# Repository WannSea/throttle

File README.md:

# WannSea Gashebel Firmware

Dieses Projekt nutzt das https://github.com/rp-rs/rp2040-project-template als Template.

## Installation

Rust über https://rustup.rs/ installieren und anschließend ausführen:

```sh
rustup target install thumbv6m-none-eabi
cargo install flip-link
cargo install --locked elf2uf2-rs
```

## Build

Es gibt zwei Möglichkeiten:

1. Den RP2040 mit gedrückter BOOTSEL-Taste per USB verbinden und die Firmware direkt bauen und flashen:

   ```sh
   cargo run
   ```

2. Eine UF2-Datei bauen, die später manuell auf das RP2040-USB-Laufwerk kopiert werden kann:

   ```sh
   cargo build --release
   elf2uf2-rs target/thumbv6m-none-eabi/release/rp2040-project-template throttle.uf2
   ```

## Info:

Green LED Blinking: Sending CAN throttle command
Red LED: Lever Locked

## Encoder / Hall

Der verwendete Encoder mit dem 5-poligen Stecker ist ein AS5600 und wird über I2C gelesen:

- Board-Stecker: `SDA`, `SCL`, `PWM/OUT`, `GND`, `3V3`
- Am AS5600: `VCC -> 3V3`, `GND -> GND`, `SDA -> SDA`, `SCL -> SCL`
- `DIR` habe ich fest mit `VCC` verbunden.
- `OUT/PWM` wird von der Firmware aktuell nicht benutzt.

## Veränderbare Parameter

Die wichtigsten Parameter stehen am Anfang von `src/main.rs`:

- `MAX_CURRENT_A`: maximal ausgegebener Strom bei vollständig ausgelenktem Gashebel, aktuell `500.0` A.
- `DELAY_MS`: Zeit zwischen zwei Ausgaben. `20` ms entsprechen 50 Hz.
- `ENCODER_ZERO_RAW`: Raw-Wert des Encoders in der neutralen Hebelposition.
- `ENCODER_FORWARD_MAX_RAW`: Raw-Wert bei vollständig nach vorne gedrücktem Gashebel.
- `ENCODER_REVERSE_MAX_RAW`: Raw-Wert bei vollständig nach hinten gedrücktem Gashebel.
- `ENCODER_DEADZONE_COUNTS`: Totzone von der Neutralstellung aus in jede Richtung. `50` bedeutet ungefähr 100 Counts Gesamttotzone.
- `PRETEND_HALL_PIN_ON`: Bei `true` wird der Hall-/Kill-Cord-Eingang für Tests als dauerhaft vorhanden behandelt.
- `ENABLE_USB_LOGGING`: Aktiviert bei `true` die Ausgabe der Encoderwerte über USB-Serial.

Die Encoder-Endwerte dürfen je nach Einbaurichtung des Sensors größer oder kleiner als `ENCODER_ZERO_RAW` sein. Entscheidend ist, dass die Werte an den tatsächlichen Endpositionen des Hebels eingetragen werden.

## USB-Debug-Ausgabe

Bei aktiviertem `ENABLE_USB_LOGGING` wird beispielsweise folgende Zeile ausgegeben:

```text
encoder raw: 2237, throttle_milli: 0, can: 00000116#00000000
```

Die drei Werte bedeuten:

- `encoder raw`: unverarbeiteter 12-Bit-Messwert des AS5600 von `0` bis `4095`.
- `throttle_milli`: aus Kalibrierung und Totzone berechnete Gasstellung. `-1000` entspricht dem einen Endanschlag, `0` der Neutralstellung und `+1000` dem anderen Endanschlag.
- `can`: Vorschau der tatsächlich gesendeten CAN-Nachricht im Format `CAN-ID#Payload`. `00000116` ist die `SetCurrent`-Nachricht für VESC-ID 22. Der achtstellige Payload enthält den vorzeichenbehafteten Stromwert als Ampere × 1.000. Im gesperrten Zustand ist dieser Payload immer `00000000`.

## SetDuty- und SetCurrent-Version

| SetDuty-Version | Aktuelle SetCurrent-Version |
|---|---|
| VESC `SetDuty`, CAN-ID `0x16` | VESC `SetCurrent`, CAN-ID `0x116` |
| Payload: vorzeichenbehafteter Duty-Wert von −100.000 bis +100.000 | Payload: vorzeichenbehafteter Stromwert von −500.000 bis +500.000 (Ampere × 1.000) |
| 50 Werte großes Glättungsfenster | Keine Glättung und keine Rampe |
| Vollständige Rampe dauert ca. 1 Sekunde | Ausgang folgt dem Gashebel unmittelbar |
| Ausgabe alle 20 ms / 50 Hz | Ausgabe alle 20 ms / 50 Hz |
| Null und der gesperrte Zustand werden explizit gesendet | Null und der gesperrte Zustand werden explizit gesendet |
| Encoder- und Hall-Auswertung wie in der aktuellen Version | Encoder- und Hall-Auswertung unverändert |

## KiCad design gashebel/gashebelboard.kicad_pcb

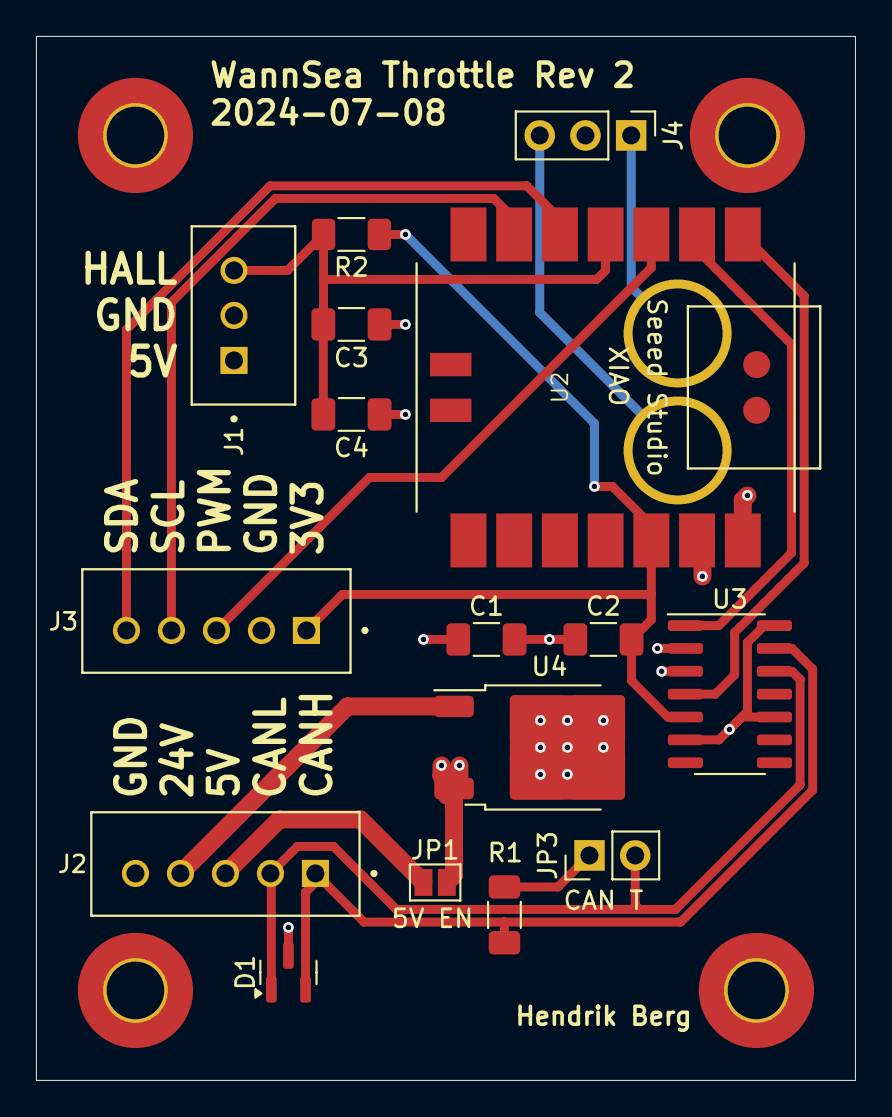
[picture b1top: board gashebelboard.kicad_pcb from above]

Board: 4 copper layers, 45.5 x 58.0 mm, 20 parts (0 on the bottom side), 16 nets.

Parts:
C1, C2: 10µ; C_1206_3216Metric_Pad1.33x1.80mm_HandSolder
C3, C4: 4.7nF; C_1206_3216Metric_Pad1.33x1.80mm_HandSolder
D1: SM712_SOT23; SOT-23
H1, H2, H3, H4: MountingHole_Pad; MountingHole_3.2mm_M3_Pad_TopBottom
J1: Hall; JST_B3B-XH-A
J2: BOOT BUS; JST_B5B-XH-A
J3: ENCODER; JST_B5B-XH-A
J4: Conn_01x03_Pin; PinHeader_1x03_P2.54mm_Vertical
JP1: 5V EN; SolderJumper-2_P1.3mm_Open_Pad1.0x1.5mm
JP3: CAN T; PinHeader_1x02_P2.54mm_Vertical
R1: 120; R_1206_3216Metric_Pad1.30x1.75mm_HandSolder
R2: 1.2K; R_1206_3216Metric_Pad1.30x1.75mm_HandSolder
U2: Seeed Studio XIAO SAMD21; XIAO-SAMD21-RP2040-14P-2.54-21X17.8MM (Seeeduino XIAO)
U3: TJA1043T; SOIC-14_3.9x8.7mm_P1.27mm
U4: LM78M05_TO252; TO-252-2

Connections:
+3.3V: C2.2, J3.1, R2.1, U2.12 (3V3), U3.5 (VIO)
+5V: C1.1, C3.1, J1.1, JP1.2 (B), U2.14 (5V), U3.3 (VCC), U3.6 (EN), U3.10 (VBAT), U3.14 (~STB), U4.3 (VO)
/CAN_RX: U2.1 (PA02_A0_D0), U3.4 (RXD)
/CAN_TX: U2.2 (PA4_A1_D1), U3.1 (TXD)
/HALL: C3.2, C4.2, J1.3, R2.2, U2.4 (PA11_A3_D3)
/PWM: J3.3, U2.3 (PA10_A2_D2)
/SCL: J3.4, U2.6 (PA9_A5_D5_SCL)
/SDA: J3.5, U2.5 (PA8_A4_D4_SDA)
GND: C1.2, C2.1, C4.1, D1.3 (common), H1.1, H2.1, H3.1, H4.1, J1.2, J2.5, J3.2, J4.2, U2.13 (GND), U3.2 (GND), U4.2 (GND)
unnamed: D1.1 (A1), J2.2, JP3.2 (B), U3.12 (CANL)
unnamed: D1.2 (A2), J2.1, R1.1, U3.13 (CANH)
unnamed: J2.3, JP1.1 (A)
unnamed: J2.4, U4.1 (VI)
unnamed: J4.1, U2.17 (PA31_SWDIO)
unnamed: J4.3, U2.18 (PA30_SWCLK)
unnamed: JP3.1 (A), R1.2

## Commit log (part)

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2024-06-25 add kill cord function
2024-06-26 move to wannsea can2040 package
2024-06-28 adjust angles
2024-07-02 adjust throttle map
2025-06-11 recalibrate
2025-06-11 add doc
2025-12-10 formatting
2025-12-10 add schematics
2026-06-18 Calibration guide added
2026-06-18 Duty ersetzt durch erpm und current
2026-06-18 Reverse and forward different accellerations
2026-06-18 Usb-logging implemented
2026-06-21 Hall sensor check toggle
2026-06-21 duty mode back in
2026-06-21 attempt to fix
